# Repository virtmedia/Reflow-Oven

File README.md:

# Reflow-Oven
Simple DIY reflow soldering oven controller with 16x2 LCD, Encoder &amp; K thermocouple
 Main components:
 -Atmega88
 -LCD 16x2 on HD44780
 -Rotary encoder with switch
 -MAX6675 thermocouple interface
 -Digital out for optotriac or relay module (with transistor)
 -buzzer
 
 Simple PCB for make at home (one layer, thick routes)
 
 Current project etap: Writing code.

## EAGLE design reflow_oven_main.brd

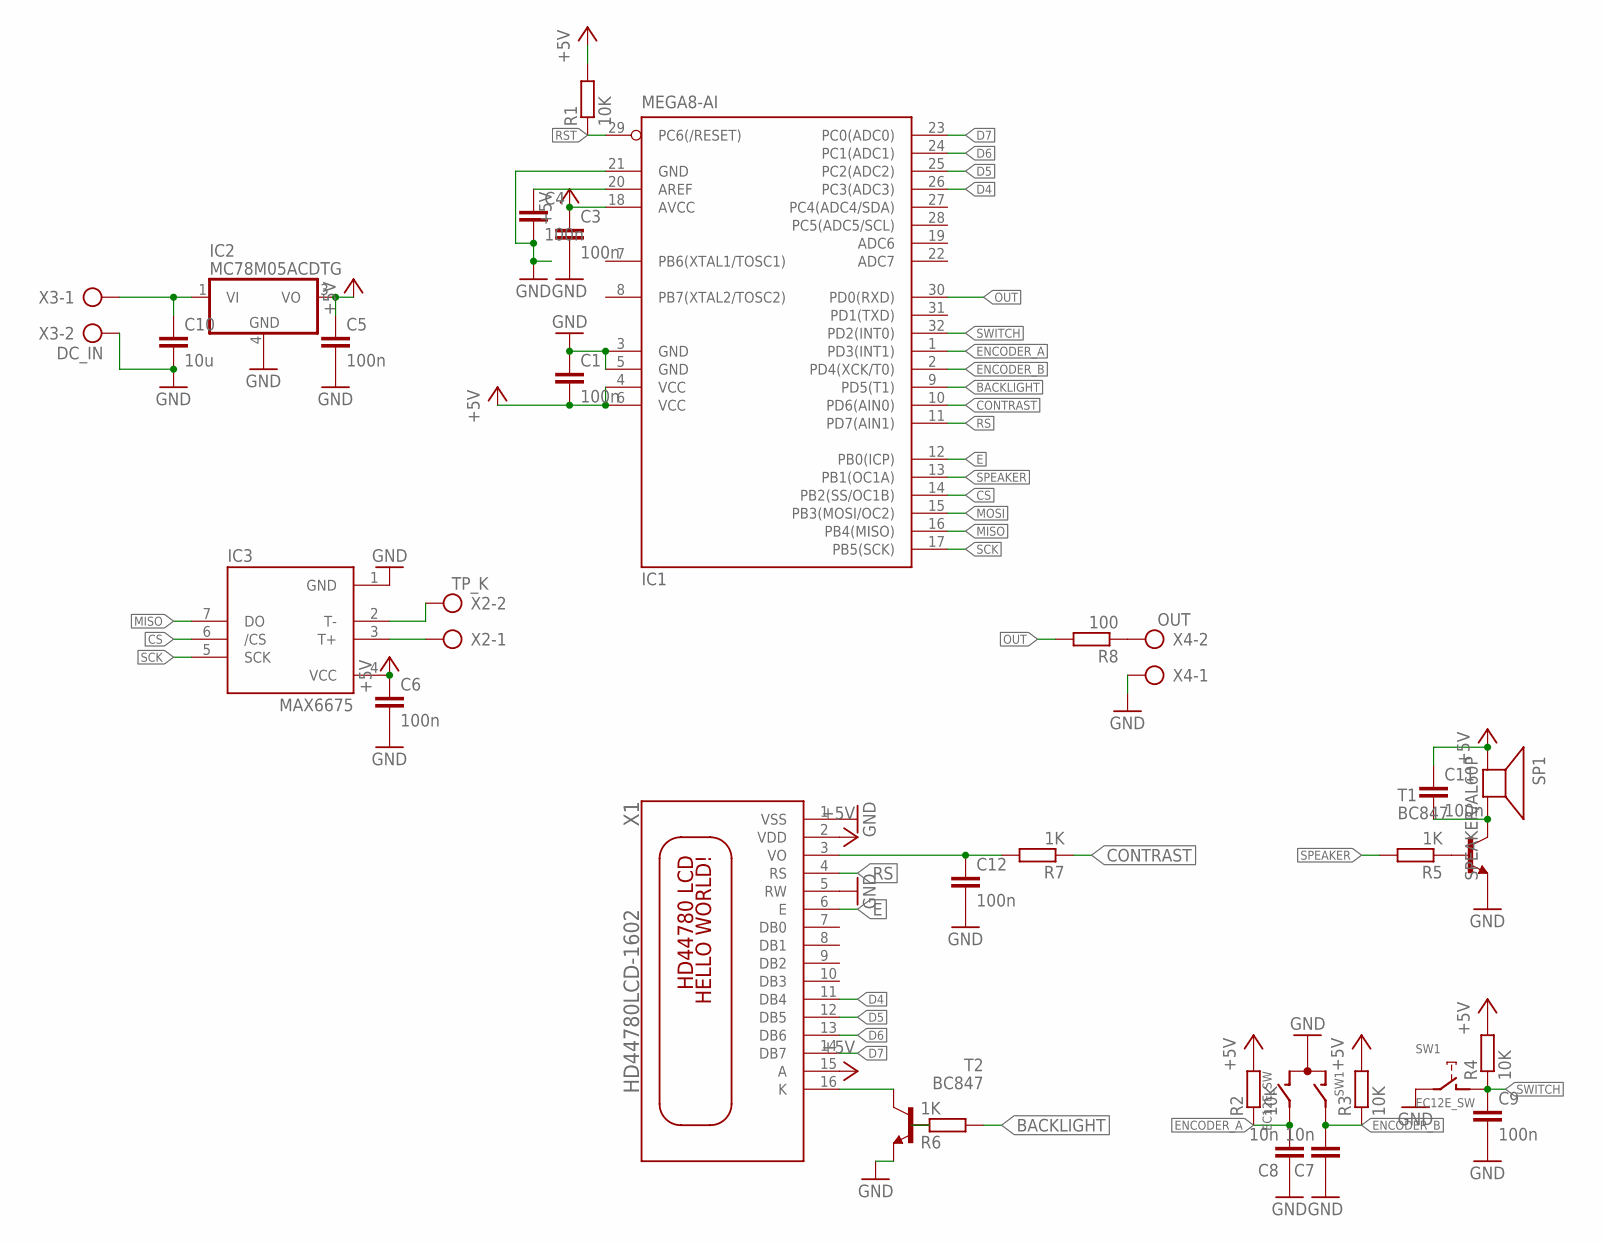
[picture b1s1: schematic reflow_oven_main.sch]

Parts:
C1, C3, C4, C5, C6, C9, C11, C12: 100n; C0603
C7, C8: 10n; C0603
C10: 10u; C0805
IC1: MEGA8-AI; TQFP32-08
IC2: MC78M05ACDTG; DPACK_3
IC3: MAX6675; SO08
R1, R2, R3, R4: 10K; R0603
R5, R6, R7: 1K; R0603
R8: 100; R0603
SP1: SPEAKER/AL60P; AL60P
SW1: EC12E_SW; ALPS_EC12E_SW
T1, T2: BC847; SOT23
X1: HD44780LCD-1602; LCD1602
X2: TP_K; AK500/2
X3: DC_IN; AK500/2
X4: OUT; AK500/2

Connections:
+5V: C1.2, C3.1, C5.1, C6.1, C11.1, IC1.4 (VCC), IC1.6 (VCC), IC1.18 (AVCC), IC2.3 (VO), IC3.4 (VCC), R1.2, R2.2, R3.2, R4.2, SP1.1 (+), X1.2 (VDD), X1.15 (A)
BACKLIGHT: IC1.9 (PD5(T1)), R6.2
CONTRAST: IC1.10 (PD6(AIN0)), R7.1
CS: IC1.14 (PB2(SS/OC1B)), IC3.6 (/CS)
D4: IC1.26 (PC3(ADC3)), X1.11 (DB4)
D5: IC1.25 (PC2(ADC2)), X1.12 (DB5)
D6: IC1.24 (PC1(ADC1)), X1.13 (DB6)
D7: IC1.23 (PC0(ADC0)), X1.14 (DB7)
E: IC1.12 (PB0(ICP)), X1.6 (E)
ENCODER_A: C8.2, IC1.1 (PD3(INT1)), R2.1, SW1.B
ENCODER_B: C7.2, IC1.2 (PD4(XCK/T0)), R3.1, SW1.A
GND: C1.1, C3.2, C4.2, C5.2, C6.2, C7.1, C8.1, C9.2, C10.2, C12.2, IC1.3 (GND), IC1.5 (GND), IC1.21 (GND), IC2.4 (GND), IC3.1 (GND), SW1.C, SW1.E (2), T1.2 (E), T2.2 (E), X1.1 (VSS), X1.5 (RW), X3.2, X4.1
MISO: IC1.16 (PB4(MISO)), IC3.7 (DO)
MOSI: IC1.15 (PB3(MOSI/OC2))
unnamed: T2.3 (C), X1.16 (K)
unnamed: R8.1, X4.2
unnamed: C11.2, SP1.2 (-), T1.3 (C)
unnamed: R5.1, T1.1 (B)
unnamed: R6.1, T2.1 (B)
unnamed: C4.1, IC1.20 (AREF)
unnamed: C12.1, R7.2, X1.3 (VO)
unnamed: C10.1, IC2.1 (VI), X3.1
OUT: IC1.30 (PD0(RXD)), R8.2
RS: IC1.11 (PD7(AIN1)), X1.4 (RS)
RST: IC1.29 (PC6(/RESET)), R1.1
SCK: IC1.17 (PB5(SCK)), IC3.5 (SCK)
SPEAKER: IC1.13 (PB1(OC1A)), R5.2
SWITCH: C9.1, IC1.32 (PD2(INT0)), R4.1, SW1.D (1)
T+: IC3.3 (T+), X2.1
T-: IC3.2 (T-), X2.2

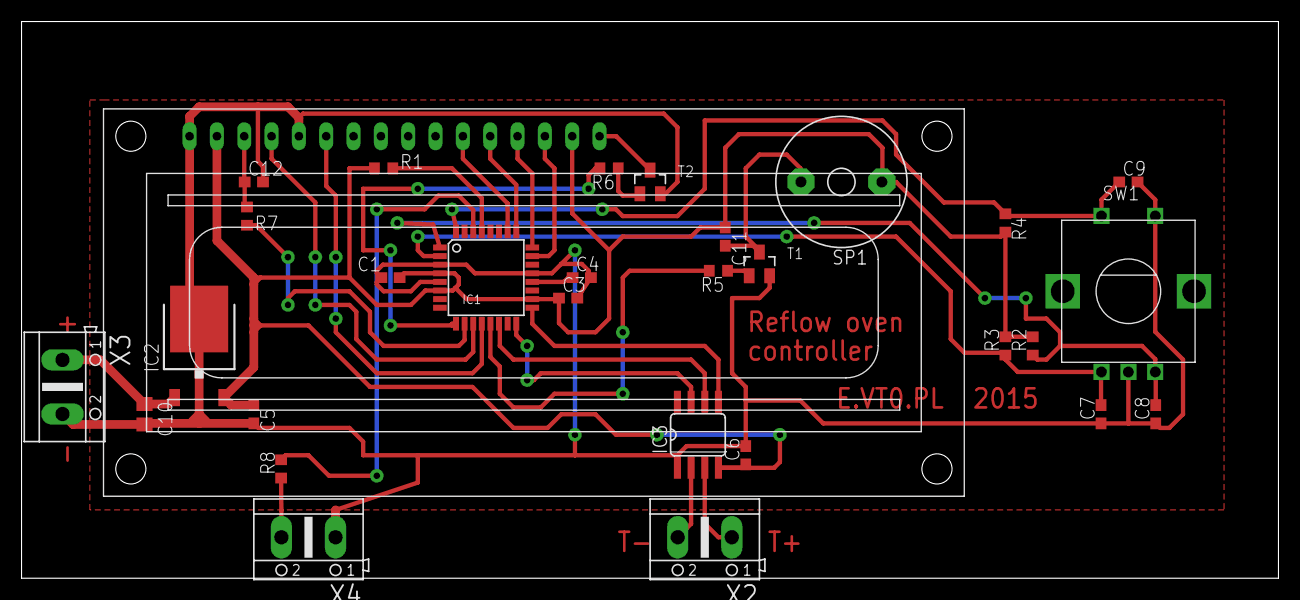
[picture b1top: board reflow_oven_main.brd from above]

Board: 2 copper layers, 116.8 x 51.7 mm, 30 parts (0 on the bottom side), 29 nets.

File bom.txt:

Partlist exported from J:/elektronika/Projekty/Wlasne/Eagle/Reflow_oven/reflow_oven_main.sch at 2015-10-20 14:21:06

Qty Value           Device          Package       Parts                            Description                                                                                                       MF MPN          OC_FARNELL OC_NEWARK
1   100             R-EU_R0603      R0603         R8                               RESISTOR, European symbol                                                                                                                             
8   100n            C-EUC0603       C0603         C1, C3, C4, C5, C6, C9, C11, C12 CAPACITOR, European symbol                                                                                                                            
4   10K             R-EU_R0603      R0603         R1, R2, R3, R4                   RESISTOR, European symbol                                                                                                                             
2   10n             C-EUC0603       C0603         C7, C8                           CAPACITOR, European symbol                                                                                                                            
1   10u             C-EUC0805       C0805         C10                              CAPACITOR, European symbol                                                                                                                            
3   1K              R-EU_R0603      R0603         R5, R6, R7                       RESISTOR, European symbol                                                                                                                             
2   BC847           BC847           SOT23         T1, T2                           45 V, 100 mA NPN general-purpose transistors                                                                                                          
1   DC_IN           AK500/2         AK500/2       X3                               CONNECTOR                                                                                                                         unknown    unknown  
1   EC12E_SW        EC12E_SW        ALPS_EC12E_SW SW1                              ALPS rotary Encoder EC12E series with switch                                                                         EC12E2424407 1520813    74M1068  
1   HD44780LCD-1602 HD44780LCD-1602 LCD1602       X1                               HD44780 LCD                                                                                                                                           
1   MAX6675         MAX6675         SO08          IC3                                                                                                                                                                                    
1   MC78M05ACDTG    MC78M05ACDTG    DPACK_3       IC2                              500 mA Positive Voltage Regulators                                                                                                                    
1   MEGA8-AI        MEGA8-AI        TQFP32-08     IC1                              MICROCONTROLLER                                                                                                      ATMEGA8-16AU 9171371    73M8863  
1   OUT             AK500/2         AK500/2       X4                               CONNECTOR                                                                                                                         unknown    unknown  
1   SPEAKER/AL60P   SPEAKER/AL60P   AL60P         SP1                              SPEAKER Source: BuerklinAdded PS12 (for part # PS1240 piezo) http://www.ladyada.net/library/pcb/eaglelibrary.html                                     
1   TP_K            AK500/2         AK500/2       X2                               CONNECTOR                                                                                                                         unknown    unknown

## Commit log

2015-10-07 :neckbeard: Added .gitattributes & .gitignore files
2015-10-07 Added Eagle files with schematic and board design
2015-10-23 added images and bom file
2015-11-17 added silkscreen design in pdf
2019-07-12 added drawing.pdf
